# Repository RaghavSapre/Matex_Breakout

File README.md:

This is a breakout board fot the Matex miniTE Flight Controller

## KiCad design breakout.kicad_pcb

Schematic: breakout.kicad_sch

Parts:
J1, J2, J3, J15, J16, J33, J34, J35, J36, J37, J38, J39, J40, J41, J42, J43, J44, J45, J46, J47, J48, J49, J50, J51, J52, J53, J54, J55, J56, J57, J58, J59, J60, J61, J62, J63, J64, J65, J66, J67, J68: Conn_01x01; SolderWirePad_1x01_SMD_1x1mm
J4, J5, J6, J7, J8, J9, J10, J11, J12, J13, J14, J19, J20, J21, J22: Conn_01x03; PinHeader_1x03_P2.54mm_Vertical
J17, J18: Conn_02x01; PinSocket_2x01_P2.54mm_Vertical
J23, J24, J25, J26, J27, J28, J29, J30, J31, J32: Conn_01x04; PinHeader_1x04_P2.54mm_Vertical
U1: Matek_mini_fte

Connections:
/gnd: J18.1, J19.3, J20.3, J21.1, J22.1, J23.4, J24.4, J25.4, J26.1, J27.1, J28.1, J29.1, J30.4, J31.4, J32.4, U1.1 (G), U1.6 (G)
unnamed: J1.1, U1.11 (R5)
unnamed: J2.1, U1.12 (T5)
unnamed: J3.1, U1.13 (4v5)
unnamed: J4.2, J5.2, J6.2, J7.2, J8.2, J65.1
unnamed: J4.3, J64.1
unnamed: J5.3, J63.1
unnamed: J6.3, J62.1
unnamed: J8.3, U1.14 (BZ-)
unnamed: J4.1, J5.1, J6.1, J7.1, J8.1, J9.1, J10.1, J11.1, J12.1, J13.1, J14.3, J39.1, U1.15 (G)
unnamed: J9.2, J10.2, J11.2, J12.2, J13.2, J37.1, J38.1, J66.1
unnamed: J10.3, J51.1
unnamed: J11.3, J52.1
unnamed: J12.3, J60.1
unnamed: J13.3, J61.1
unnamed: J14.1, U1.17 (Sbs)
unnamed: J14.2, U1.16 (4v5)
unnamed: J15.1, U1.20 (S10)
unnamed: J16.1, U1.21 (S9)
unnamed: J17.1, J32.2, J53.1
unnamed: J17.2, J32.1, J67.1
unnamed: J18.2, J32.3, J54.1
unnamed: J19.1, J20.1, U1.3 (VTx)
unnamed: J19.2, J20.2, U1.2 (10V)
unnamed: J21.2, J22.2, J25.1, J26.4, J27.4, J28.4, J29.4, J42.1, U1.5 (5V)
unnamed: J21.3, J22.3, U1.4 (Cam)
unnamed: J23.1, J30.1, J57.1
unnamed: J23.2, U1.8 (T3)
unnamed: J23.3, U1.7 (R3)
unnamed: J24.1, J31.1, J48.1
unnamed: J24.2, J46.1
unnamed: J24.3, J47.1
unnamed: J25.2, J44.1
unnamed: J25.3, J45.1
unnamed: J26.2, J27.2, J28.2, J29.2, J58.1
unnamed: J26.3, J27.3, J28.3, J29.3, J59.1
unnamed: J30.2, U1.23 (T6)
unnamed: J30.3, U1.22 (R6)
unnamed: J31.2, J55.1
unnamed: J31.3, J56.1
unnamed: J7.3, J33.1
unnamed: J34.1, U1.18 (T2)
unnamed: J35.1, U1.19 (R2)
unnamed: J36.1, J43.1
unnamed: J40.1, U1.10 (SDA)
unnamed: J41.1, U1.9 (SCl)
unnamed: J49.1, J68.1
unnamed: J9.3, J50.1

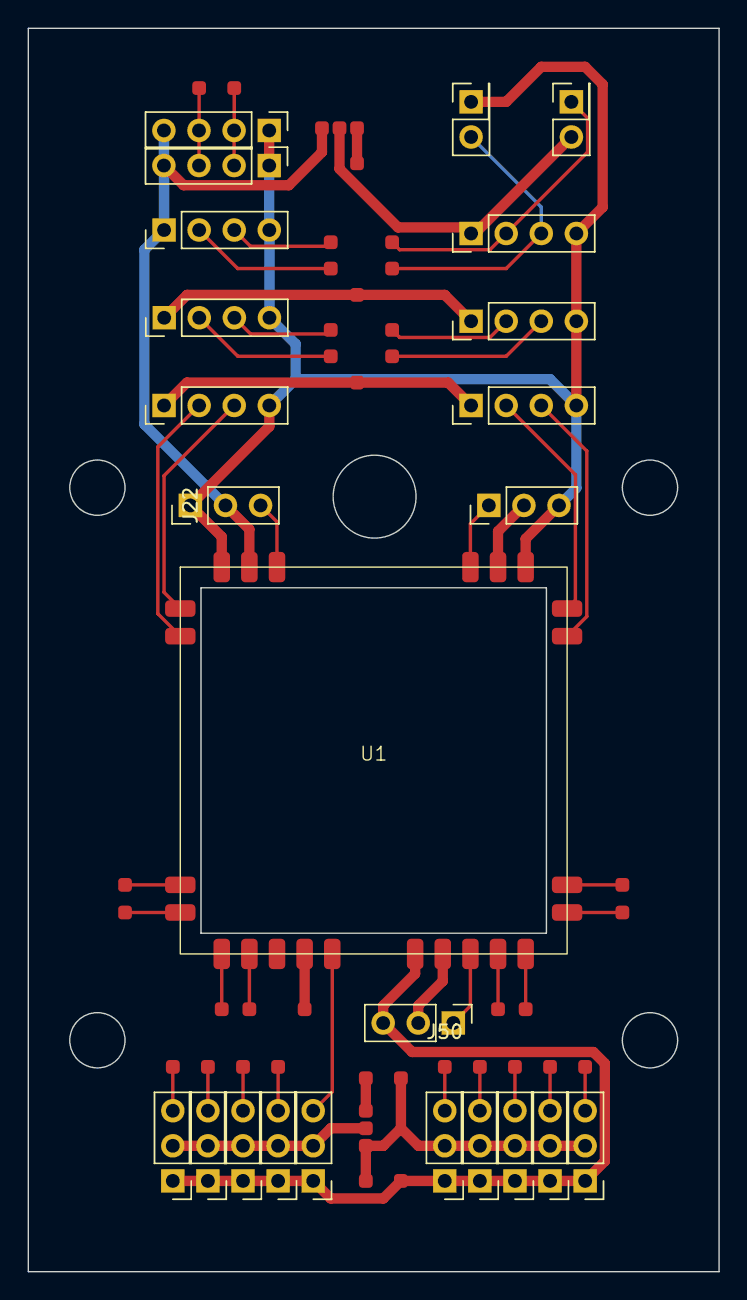
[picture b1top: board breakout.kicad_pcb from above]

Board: 2 copper layers, 50.0 x 90.0 mm, 65 parts (0 on the bottom side), 48 nets.

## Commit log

2024-07-15 Added all files
2024-07-15 Added readme
